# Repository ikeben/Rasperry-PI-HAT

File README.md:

# Rasperry-PI-HAT
This boared contains the DHT22 sensor
resistors and a a space to install a switch

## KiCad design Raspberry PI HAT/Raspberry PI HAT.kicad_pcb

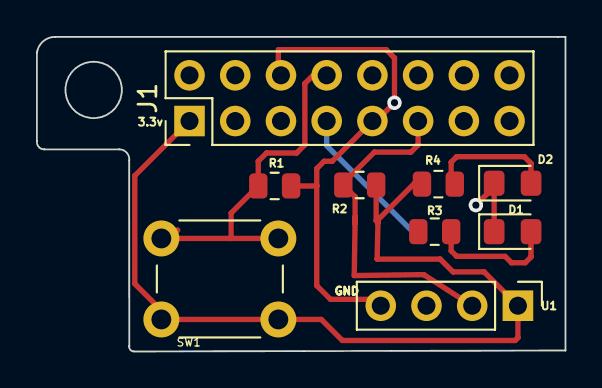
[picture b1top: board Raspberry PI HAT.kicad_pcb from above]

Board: 2 copper layers, 29.4 x 17.5 mm, 9 parts (0 on the bottom side), 7 nets.

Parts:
D1, D2: LED; LED_0805_2012Metric_Pad1.15x1.40mm_HandSolder
J1: Raspberry_Pi_2_3; PinHeader_2x08_P2.54mm_Vertical
R1, R2: 10kohm; R_0805_2012Metric
R3, R4: 330ohm; R_0805_2012Metric
SW1: SW_DPST; SW_PUSH_6mm
U1: DHT22; PinHeader_1x04_P2.54mm_Vertical

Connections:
/3.3v: J1.1 (3V3), R2.1, R4.1, SW1.1, U1.1 (VCC)
/GND: D1.1 (K), D2.1 (K), J1.6 (GND), J1.9 (GND), R1.2, U1.4 (GND)
/button input: J1.8 (GPIO14/TXD), R1.1, SW1.2
unnamed: D1.2 (A), R3.2
unnamed: D2.2 (A), R4.2
unnamed: J1.7 (GCLK0/GPIO4), R3.1
unnamed: J1.11 (GPIO17), R2.2, U1.2 (IO)
